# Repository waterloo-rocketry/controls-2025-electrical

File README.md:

2025 Controls Electrical Design
===============================

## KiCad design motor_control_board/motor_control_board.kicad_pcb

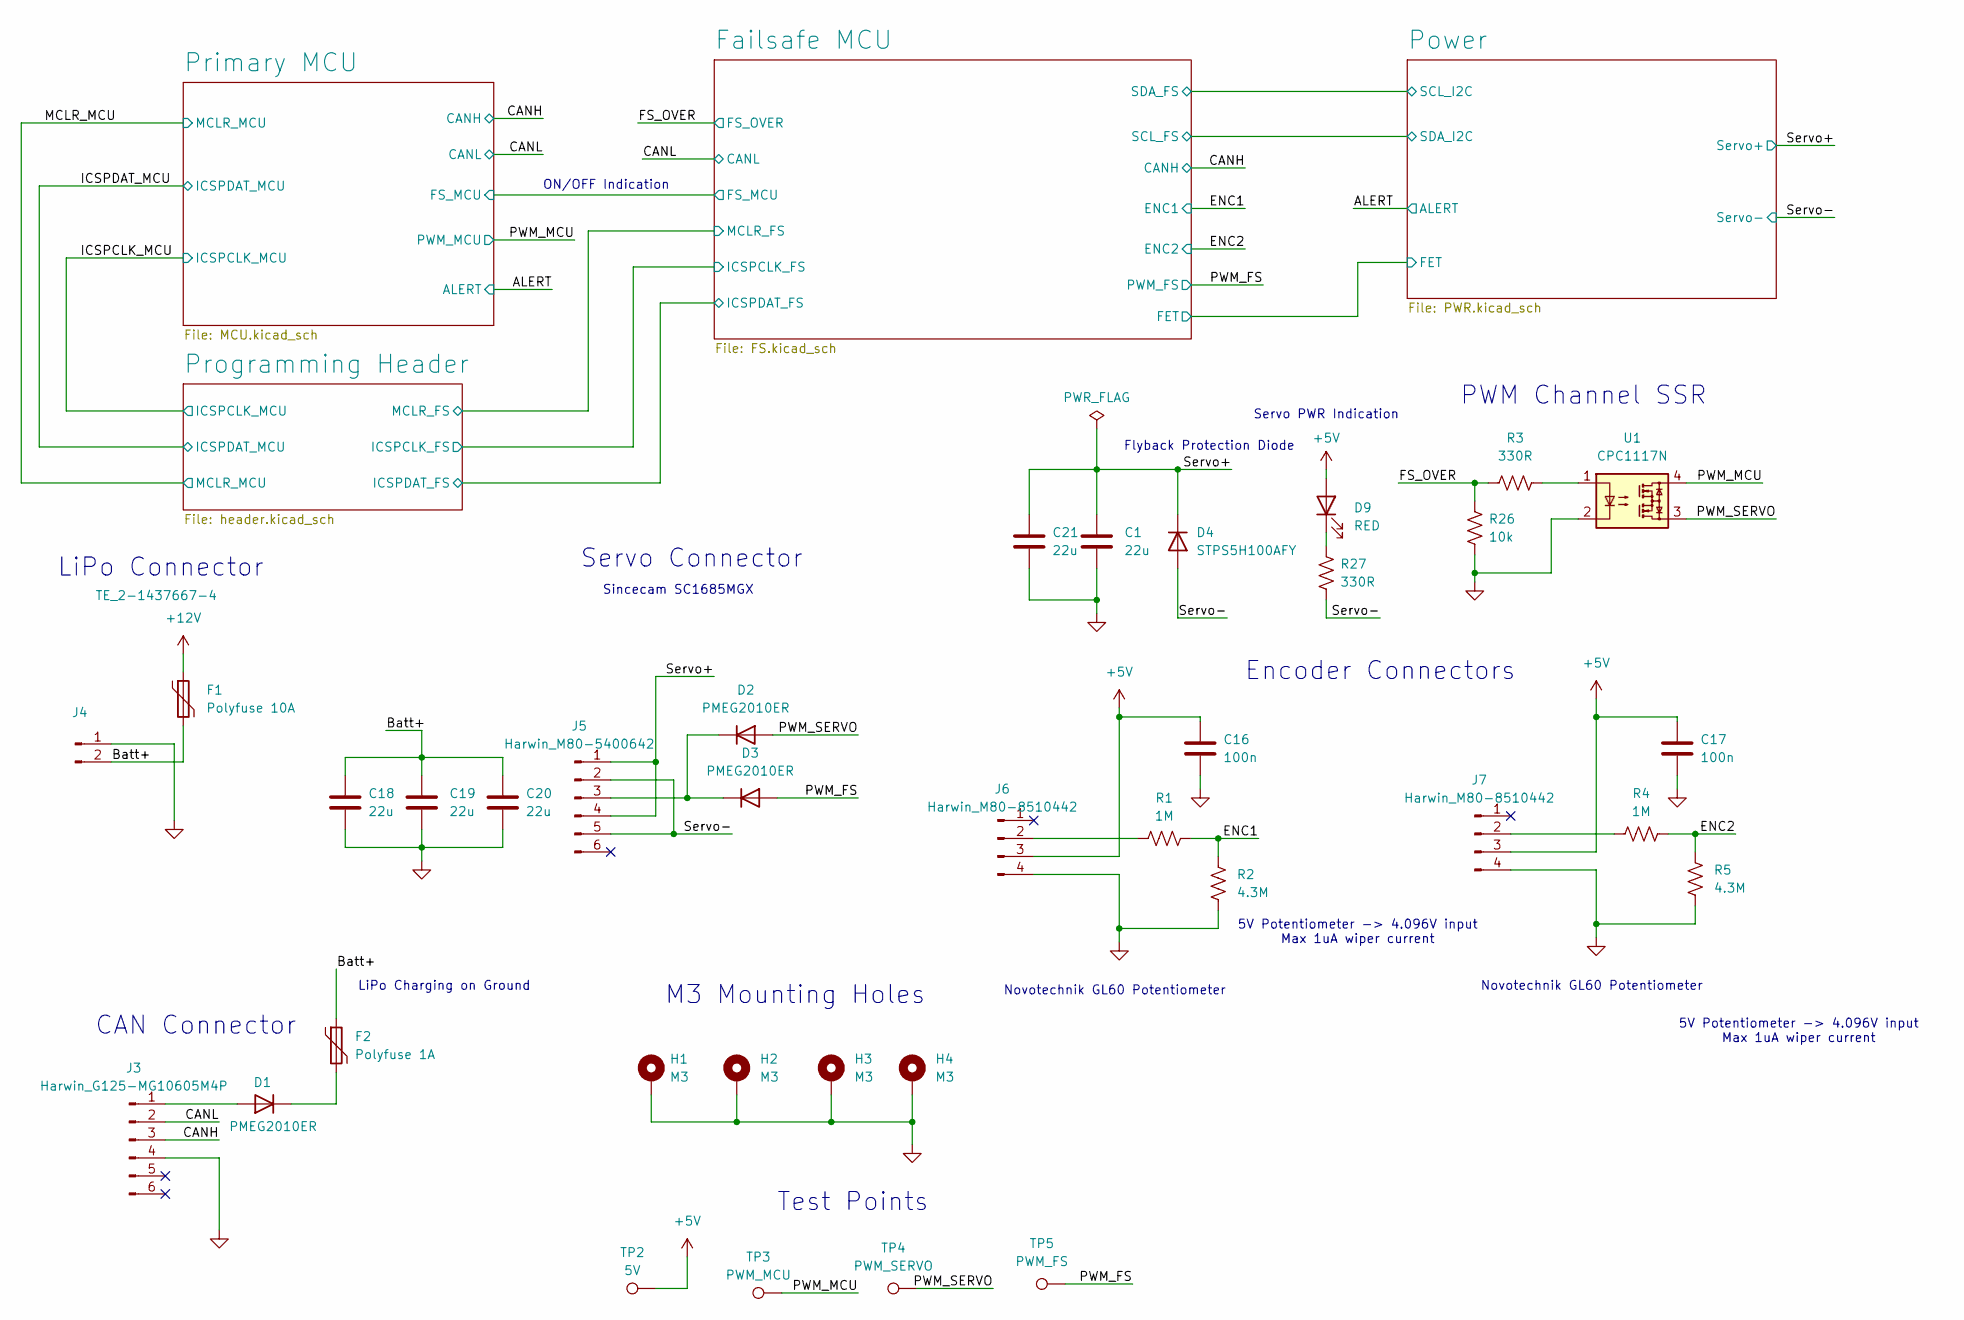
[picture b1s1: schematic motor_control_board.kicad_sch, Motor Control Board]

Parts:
C1, C18, C19, C20, C21: 22u; C_0805_2012Metric_Pad1.18x1.45mm_HandSolder
C16, C17: 100n; C_0805_2012Metric_Pad1.18x1.45mm_HandSolder
D1, D2, D3: PMEG2010ER; Nexperia_CFP3_SOD-123W
D4: STPS5H100AFY; D_SOD-128
D9: RED; LED_1206_3216Metric_Pad1.42x1.75mm_HandSolder
F1: Polyfuse 10A; Fuse_1206_3216Metric_Pad1.42x1.75mm_HandSolder
F2: Polyfuse 1A; Fuse_1206_3216Metric_Pad1.42x1.75mm_HandSolder
H1, H2, H3, H4: M3; MountingHole_3.2mm_M3_DIN965_Pad
J3: Harwin_G125-MG10605M4P; connector_Harwin_G125–MG10605M4P
J4: TE_2-1437667-4
J5: Harwin_M80-5400642; HARWIN_M80-5400642
J6, J7: Harwin_M80-8510442; HARWIN_M80-8510442
R1, R4: 1M; R_0805_2012Metric_Pad1.20x1.40mm_HandSolder
R2, R5: 4.3M; R_0805_2012Metric_Pad1.20x1.40mm_HandSolder
R3, R27: 330R; R_0805_2012Metric_Pad1.20x1.40mm_HandSolder
R26: 10k; R_0805_2012Metric_Pad1.20x1.40mm_HandSolder
TP2: 5V; TestPoint_Keystone_5000-5004_Miniature
TP3: PWM_MCU; TestPoint_Keystone_5000-5004_Miniature
TP4: PWM_SERVO; TestPoint_Keystone_5000-5004_Miniature
TP5: PWM_FS; TestPoint_Keystone_5000-5004_Miniature
U1: CPC1117N; SOIC254P610X218-4N

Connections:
+5V: C16.1, C17.1, D9.2 (A), J6.3, J7.3, TP2.1; also elsewhere on the board
+12V: F1.1; also elsewhere on the board
/Batt+: C18.1, C19.1, C20.1, F1.2, F2.1, J4.2
/CANH: J3.3; also elsewhere on the board
/CANL: J3.2; also elsewhere on the board
/ENC1: R1.2, R2.1; also elsewhere on the board
/ENC2: R4.2, R5.1; also elsewhere on the board
/FS_OVER: R3.1, R26.1; also elsewhere on the board
/PWM_FS: D3.2 (A), TP5.1; also elsewhere on the board
/PWM_MCU: TP3.1, U1.4; also elsewhere on the board
/PWM_SERVO: D2.2 (A), TP4.1, U1.3
/Servo+: C1.1, C21.1, D4.1 (K), J5.1, J5.4; also elsewhere on the board
/Servo-: D4.2 (A), J5.2, J5.5, R27.2; also elsewhere on the board
GND: C1.2, C16.2, C17.2, C18.2, C19.2, C20.2, C21.2, H1.1, H2.1, H3.1, H4.1, J3.4, J4.1, J6.4, J7.4, R2.2, R5.2, R26.2, U1.2; also elsewhere on the board
unnamed: D1.2 (A), J3.1
unnamed: D1.1 (K), F2.2
unnamed: D2.1 (K), D3.1 (K), J5.3
unnamed: D9.1 (K), R27.1
unnamed: J6.2, R1.1
unnamed: J7.2, R4.1
unnamed: R3.2, U1.1

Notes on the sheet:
Novotechnik GL60 Potentiometer
5V Potentiometer -> 4.096V input Max 1uA wiper current
Flyback Protection Diode
Servo PWR Indication
Servo Connector
M3 Mounting Holes
LiPo Charging on Ground
Sincecam SC1685MGX
ON/OFF Indication
Test Points
PWM Channel SSR
LiPo Connector
Encoder Connectors
CAN Connector

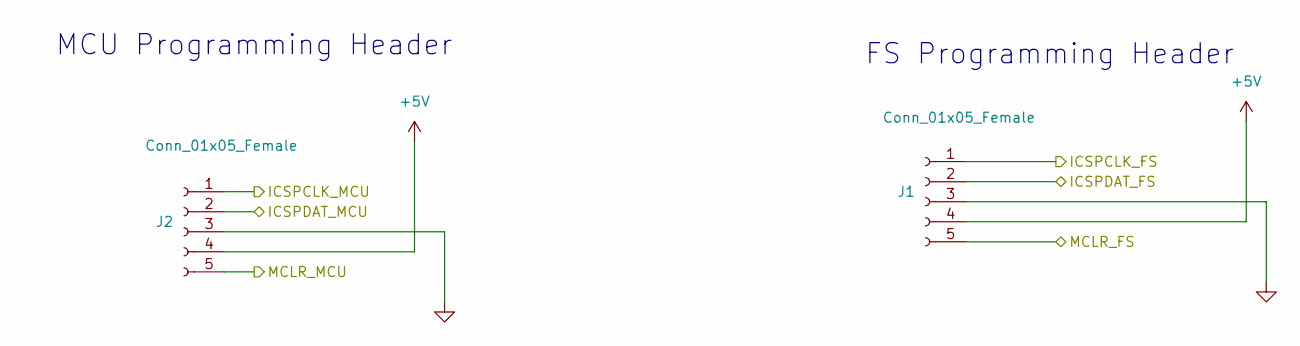
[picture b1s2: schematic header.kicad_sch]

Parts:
J1, J2: Conn_01x05_Female; PinSocket_5x2.54_SMD_90deg_952-3198-1-ND

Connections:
+5V: J1.4, J2.4; also elsewhere on the board
/Failsafe MCU/ICSPCLK_FS: J1.1; also elsewhere on the board
/Failsafe MCU/ICSPDAT_FS: J1.2; also elsewhere on the board
/Failsafe MCU/MCLR_FS: J1.5; also elsewhere on the board
/ICSPCLK_MCU: J2.1; also elsewhere on the board
/ICSPDAT_MCU: J2.2; also elsewhere on the board
/MCLR_MCU: J2.5; also elsewhere on the board
GND: J1.3, J2.3; also elsewhere on the board

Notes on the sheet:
FS Programming Header
MCU Programming Header

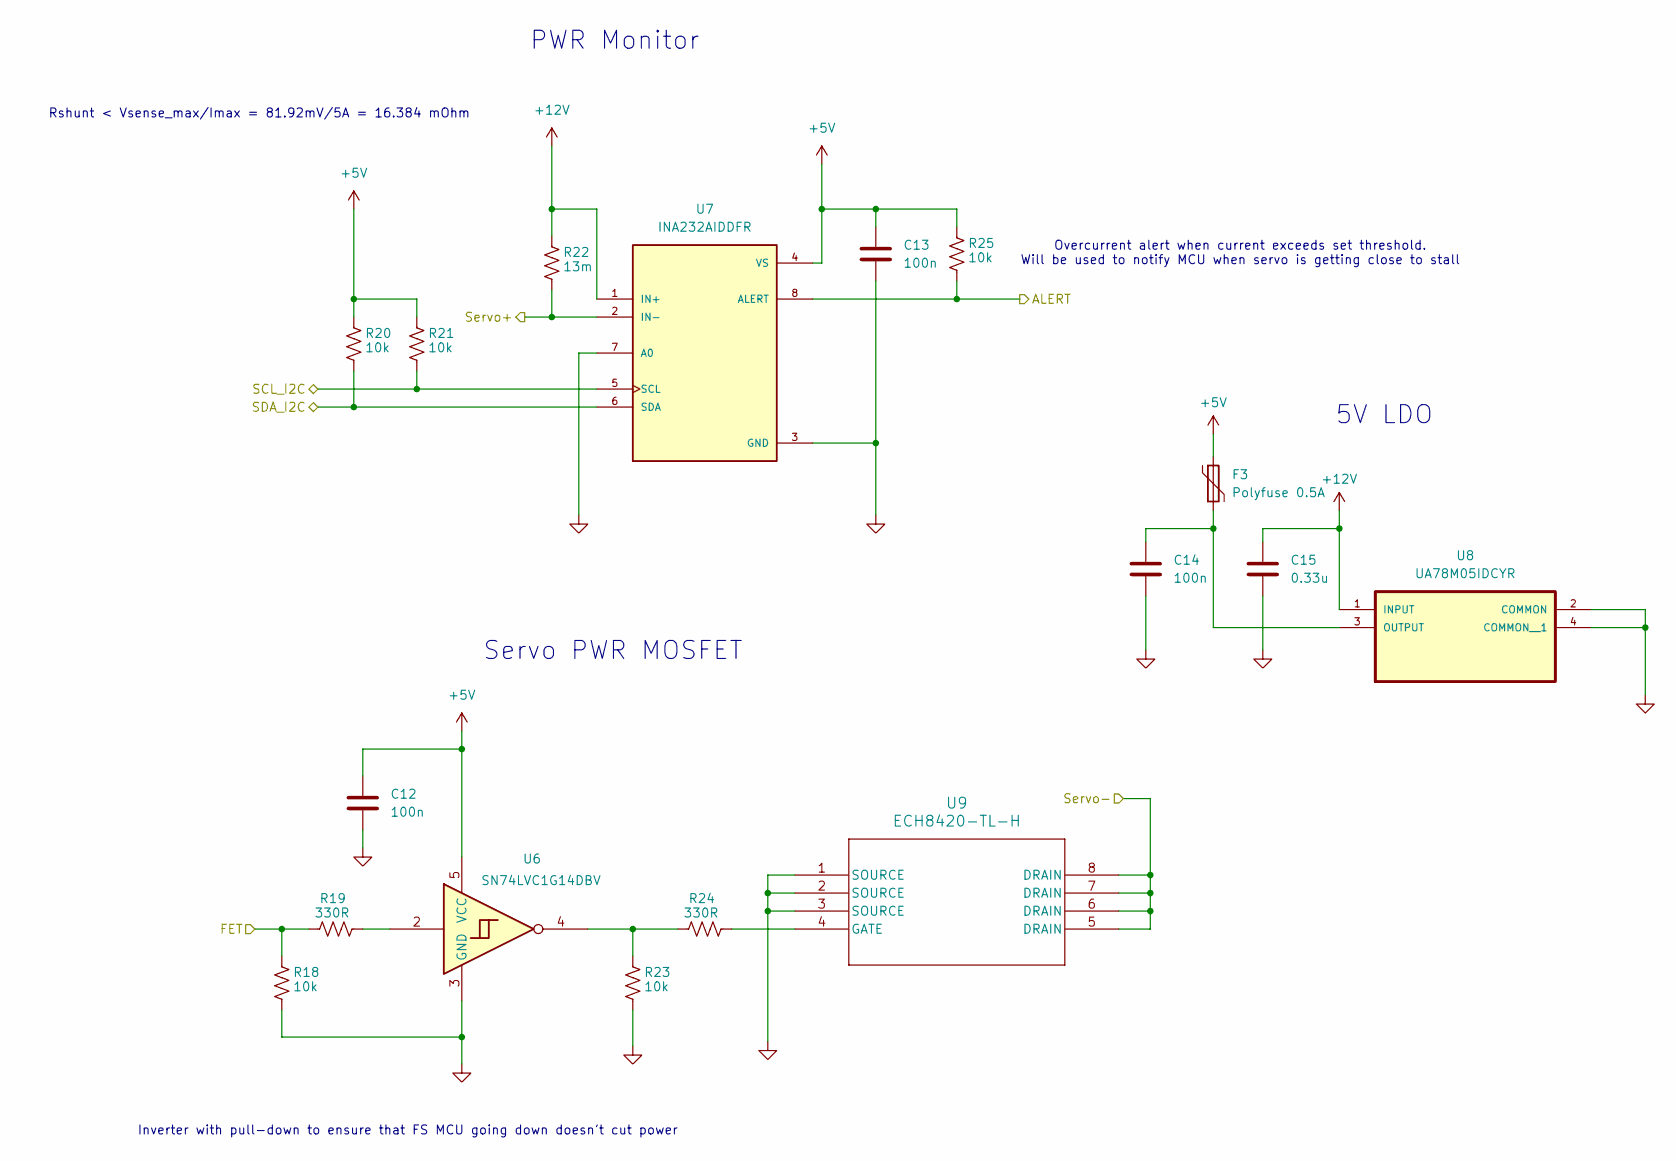
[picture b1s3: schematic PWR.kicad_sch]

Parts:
C12, C13, C14: 100n; C_0805_2012Metric_Pad1.18x1.45mm_HandSolder
C15: 0.33u; C_0805_2012Metric_Pad1.18x1.45mm_HandSolder
F3: Polyfuse 0.5A; Fuse_1206_3216Metric_Pad1.42x1.75mm_HandSolder
R18, R20, R21, R23, R25: 10k; R_0805_2012Metric_Pad1.20x1.40mm_HandSolder
R19, R24: 330R; R_0805_2012Metric_Pad1.20x1.40mm_HandSolder
R22: 13m; R_1206_3216Metric_Pad1.30x1.75mm_HandSolder
U6: SN74LVC1G14DBV; SOT-23-5
U7: INA232AIDDFR; SOT65P280X110-8N; PARTREV December 2022
U8: UA78M05IDCYR; SOT230P700X180-4N
U9: ECH8420-TL-H; OnSemi_ECH8

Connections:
+5V: C12.1, C13.1, F3.1, R20.1, R21.1, R25.1, U6.5 (VCC), U7.4 (VS); also elsewhere on the board
+12V: C15.1, R22.1, U7.1 (IN+), U8.1 (INPUT); also elsewhere on the board
/ALERT: R25.2, U7.8 (ALERT); also elsewhere on the board
/Failsafe MCU/FET: R18.1, R19.1; also elsewhere on the board
/Failsafe MCU/SCL_FS: R20.2, U7.6 (SDA); also elsewhere on the board
/Failsafe MCU/SDA_FS: R21.2, U7.5 (SCL); also elsewhere on the board
/Servo+: R22.2, U7.2 (IN-); also elsewhere on the board
/Servo-: U9.5 (DRAIN), U9.6 (DRAIN), U9.7 (DRAIN), U9.8 (DRAIN); also elsewhere on the board
GND: C12.2, C13.2, C14.2, C15.2, R18.2, R23.2, U6.3 (GND), U7.3 (GND), U7.7 (A0), U8.2 (COMMON), U8.4 (COMMON__1), U9.1 (SOURCE), U9.2 (SOURCE), U9.3 (SOURCE); also elsewhere on the board
unnamed: R19.2, U6.2
unnamed: R23.1, R24.1, U6.4
unnamed: C14.1, F3.2, U8.3 (OUTPUT)
unnamed: R24.2, U9.4 (GATE)

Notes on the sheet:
Servo PWR MOSFET
PWR Monitor
Inverter with pull-down to ensure that FS MCU going down doesn't cut power
5V LDO
Overcurrent alert when current exceeds set threshold. Will be used to notify MCU when servo is getting close to stall
Rshunt < Vsense_max/Imax = 81.92mV/5A = 16.384 mOhm

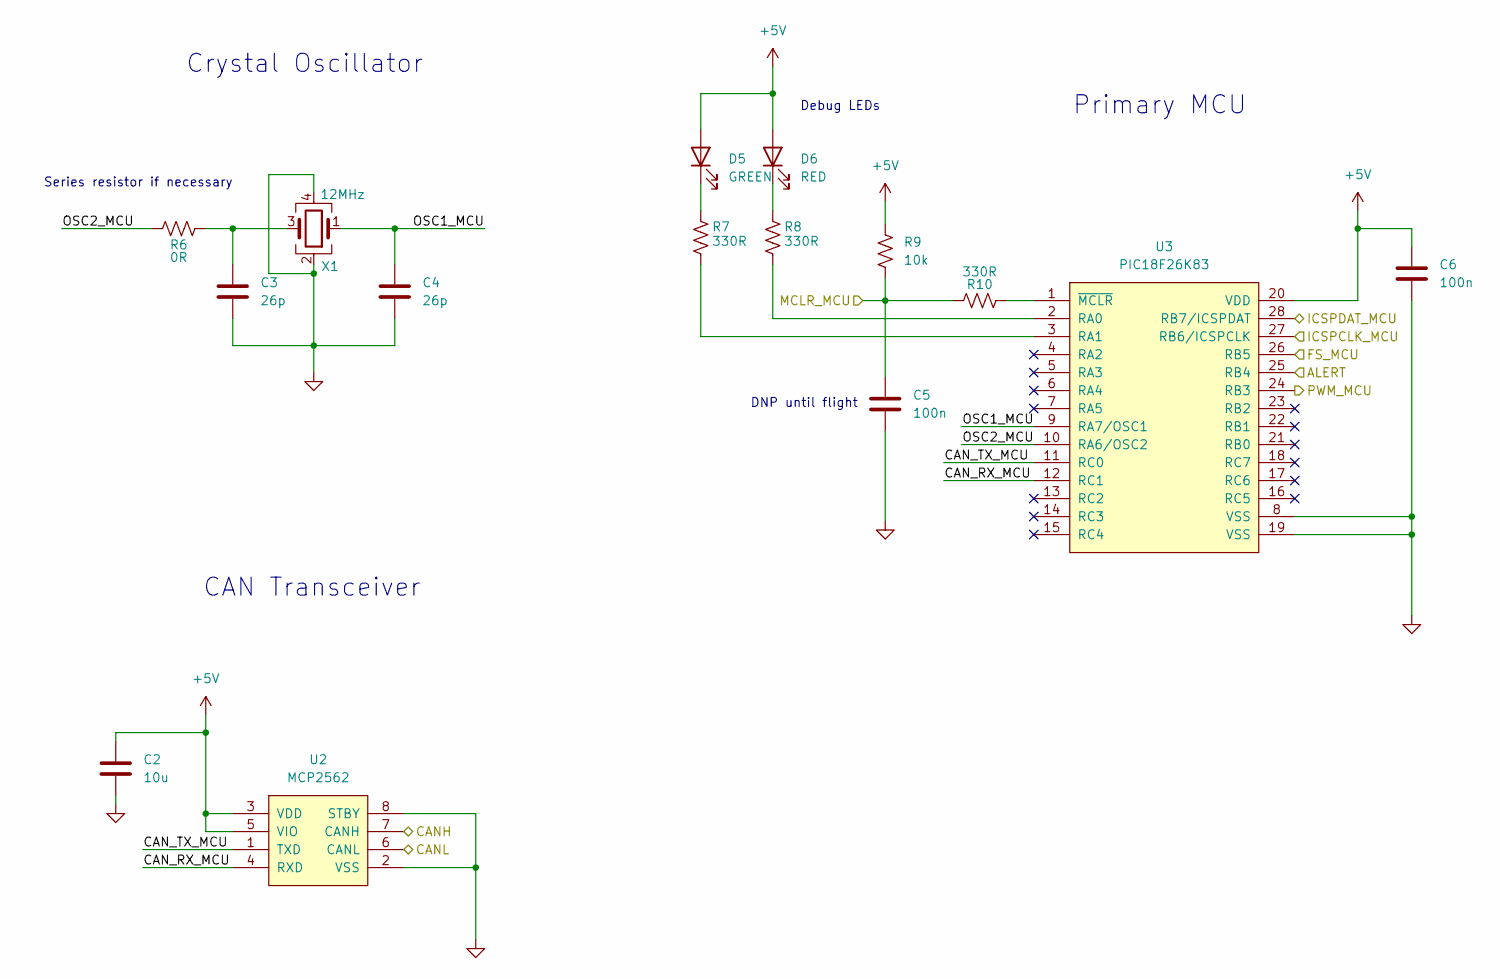
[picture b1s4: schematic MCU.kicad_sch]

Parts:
C2: 10u; C_0805_2012Metric_Pad1.18x1.45mm_HandSolder
C3, C4: 26p; C_0805_2012Metric_Pad1.18x1.45mm_HandSolder
C5, C6: 100n; C_0805_2012Metric_Pad1.18x1.45mm_HandSolder
D5: GREEN; LED_1206_3216Metric_Pad1.42x1.75mm_HandSolder
D6: RED; LED_1206_3216Metric_Pad1.42x1.75mm_HandSolder
R6: 0R; R_0805_2012Metric_Pad1.20x1.40mm_HandSolder
R7, R8, R10: 330R; R_0805_2012Metric_Pad1.20x1.40mm_HandSolder
R9: 10k; R_0805_2012Metric_Pad1.20x1.40mm_HandSolder
U2: MCP2562; SOIC-8_3.9x4.9mm_P1.27mm
U3: PIC18F26K83; SSOP-28_5.3x10.2mm_P0.65mm
X1: 12MHz; Crystal_SMD_Abracon_ABM8G-4Pin_3.2x2.5mm

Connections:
+5V: C2.1, C6.1, D5.2 (A), D6.2 (A), R9.1, U2.3 (VDD), U2.5 (VIO), U3.20 (VDD); also elsewhere on the board
/ALERT: U3.25 (RB4); also elsewhere on the board
/CANH: U2.7 (CANH); also elsewhere on the board
/CANL: U2.6 (CANL); also elsewhere on the board
/Failsafe MCU/FS_MCU: U3.26 (RB5); also elsewhere on the board
/ICSPCLK_MCU: U3.27 (RB6/ICSPCLK); also elsewhere on the board
/ICSPDAT_MCU: U3.28 (RB7/ICSPDAT); also elsewhere on the board
/MCLR_MCU: C5.1, R9.2, R10.2; also elsewhere on the board
/PWM_MCU: U3.24 (RB3); also elsewhere on the board
/Primary MCU/CAN_RX_MCU: U2.4 (RXD), U3.12 (RC1)
/Primary MCU/CAN_TX_MCU: U2.1 (TXD), U3.11 (RC0)
/Primary MCU/OSC1_MCU: C4.1, U3.9 (RA7/OSC1), X1.1
/Primary MCU/OSC2_MCU: R6.1, U3.10 (RA6/OSC2)
GND: C2.2, C3.2, C4.2, C5.2, C6.2, U2.2 (VSS), U2.8 (STBY), U3.8 (VSS), U3.19 (VSS), X1.2, X1.4; also elsewhere on the board
unnamed: C3.1, R6.2, X1.3
unnamed: D5.1 (K), R7.1
unnamed: D6.1 (K), R8.1
unnamed: R8.2, U3.2 (RA0)
unnamed: R7.2, U3.3 (RA1)
unnamed: R10.1, U3.1 (~MCLR)

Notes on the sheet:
DNP until flight
Series resistor if necessary
Crystal Oscillator
Primary MCU
CAN Transceiver
Debug LEDs

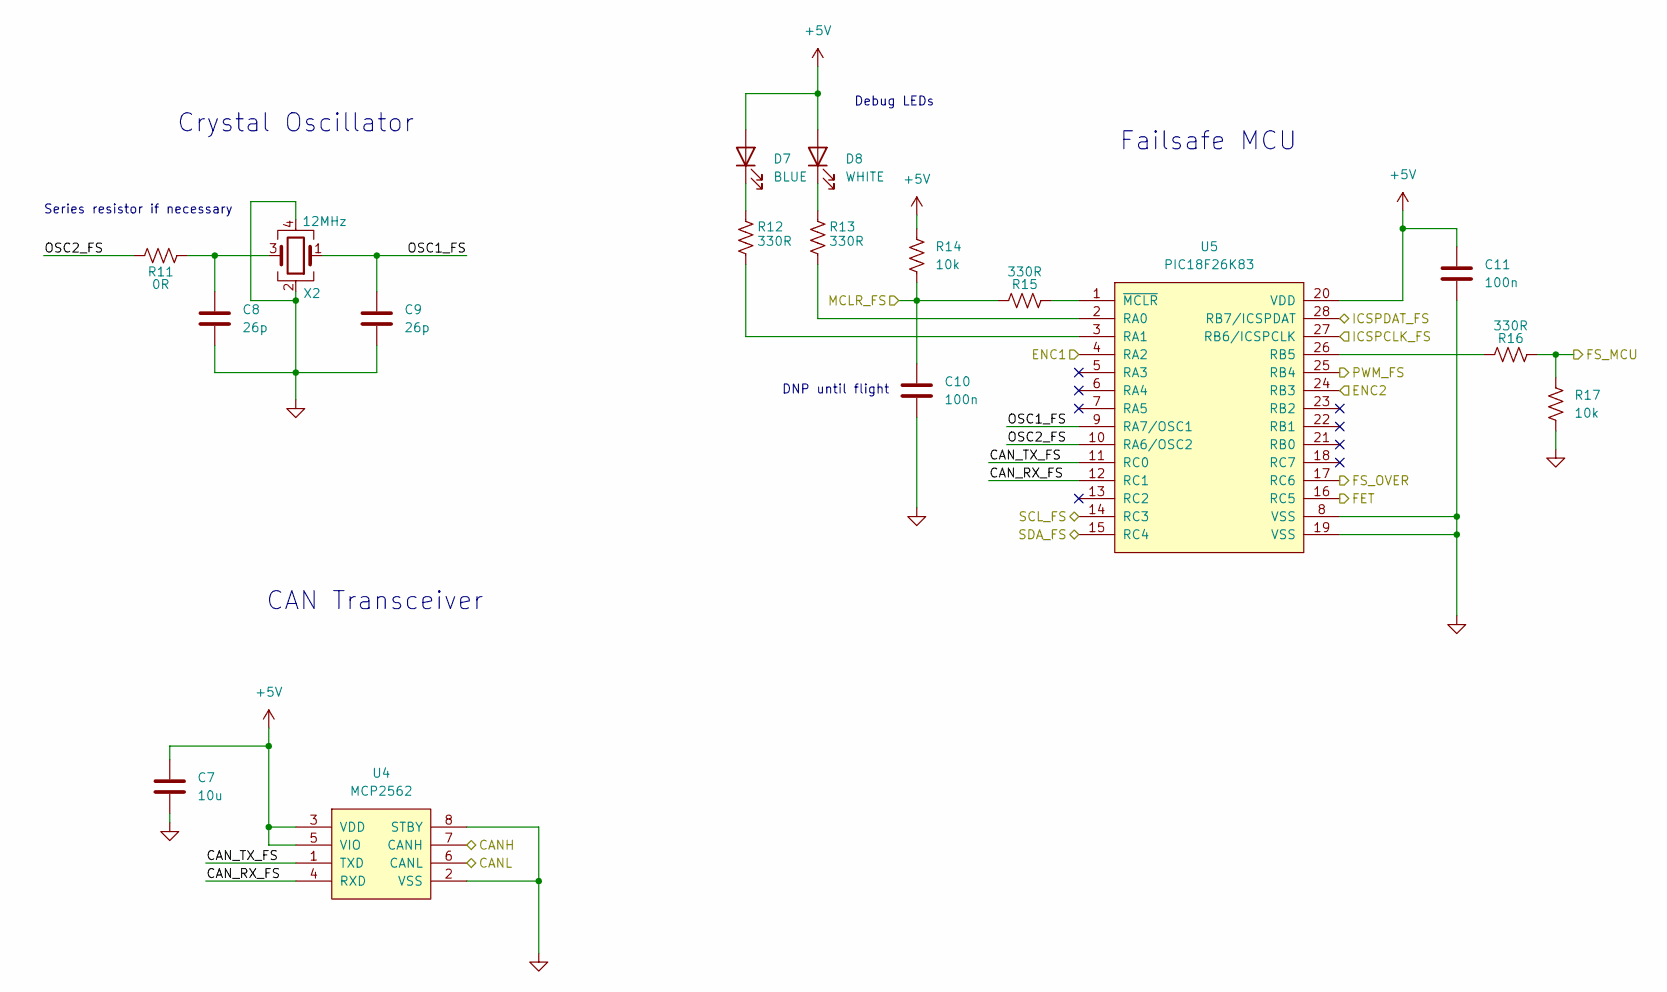
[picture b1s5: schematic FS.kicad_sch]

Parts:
C7: 10u; C_0805_2012Metric_Pad1.18x1.45mm_HandSolder
C8, C9: 26p; C_0805_2012Metric_Pad1.18x1.45mm_HandSolder
C10, C11: 100n; C_0805_2012Metric_Pad1.18x1.45mm_HandSolder
D7: BLUE; LED_1206_3216Metric_Pad1.42x1.75mm_HandSolder
D8: WHITE; LED_1206_3216Metric_Pad1.42x1.75mm_HandSolder
R11: 0R; R_0805_2012Metric_Pad1.20x1.40mm_HandSolder
R12, R13, R15, R16: 330R; R_0805_2012Metric_Pad1.20x1.40mm_HandSolder
R14, R17: 10k; R_0805_2012Metric_Pad1.20x1.40mm_HandSolder
U4: MCP2562; SOIC-8_3.9x4.9mm_P1.27mm
U5: PIC18F26K83; SSOP-28_5.3x10.2mm_P0.65mm
X2: 12MHz; Crystal_SMD_Abracon_ABM8G-4Pin_3.2x2.5mm

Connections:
+5V: C7.1, C11.1, D7.2 (A), D8.2 (A), R14.1, U4.3 (VDD), U4.5 (VIO), U5.20 (VDD); also elsewhere on the board
/CANH: U4.7 (CANH); also elsewhere on the board
/CANL: U4.6 (CANL); also elsewhere on the board
/ENC1: U5.4 (RA2); also elsewhere on the board
/ENC2: U5.24 (RB3); also elsewhere on the board
/FS_OVER: U5.17 (RC6); also elsewhere on the board
/Failsafe MCU/CAN_RX_FS: U4.4 (RXD), U5.12 (RC1)
/Failsafe MCU/CAN_TX_FS: U4.1 (TXD), U5.11 (RC0)
/Failsafe MCU/FET: U5.16 (RC5); also elsewhere on the board
/Failsafe MCU/FS_MCU: R16.1, R17.1; also elsewhere on the board
/Failsafe MCU/ICSPCLK_FS: U5.27 (RB6/ICSPCLK); also elsewhere on the board
/Failsafe MCU/ICSPDAT_FS: U5.28 (RB7/ICSPDAT); also elsewhere on the board
/Failsafe MCU/MCLR_FS: C10.1, R14.2, R15.2; also elsewhere on the board
/Failsafe MCU/OSC1_FS: C9.1, U5.9 (RA7/OSC1), X2.1
/Failsafe MCU/OSC2_FS: R11.1, U5.10 (RA6/OSC2)
/Failsafe MCU/SCL_FS: U5.14 (RC3); also elsewhere on the board
/Failsafe MCU/SDA_FS: U5.15 (RC4); also elsewhere on the board
/PWM_FS: U5.25 (RB4); also elsewhere on the board
GND: C7.2, C8.2, C9.2, C10.2, C11.2, R17.2, U4.2 (VSS), U4.8 (STBY), U5.8 (VSS), U5.19 (VSS), X2.2, X2.4; also elsewhere on the board
unnamed: C8.1, R11.2, X2.3
unnamed: D7.1 (K), R12.1
unnamed: D8.1 (K), R13.1
unnamed: R13.2, U5.2 (RA0)
unnamed: R12.2, U5.3 (RA1)
unnamed: R16.2, U5.26 (RB5)
unnamed: R15.1, U5.1 (~MCLR)

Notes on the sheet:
Failsafe MCU
Crystal Oscillator
CAN Transceiver
Debug LEDs
DNP until flight
Series resistor if necessary

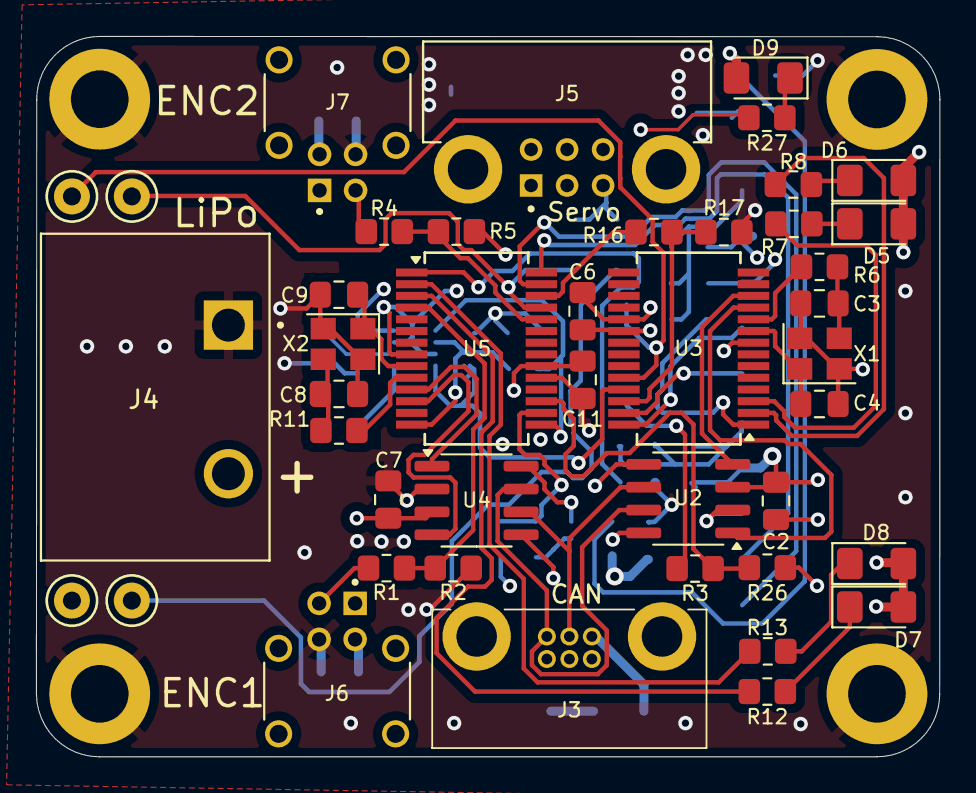
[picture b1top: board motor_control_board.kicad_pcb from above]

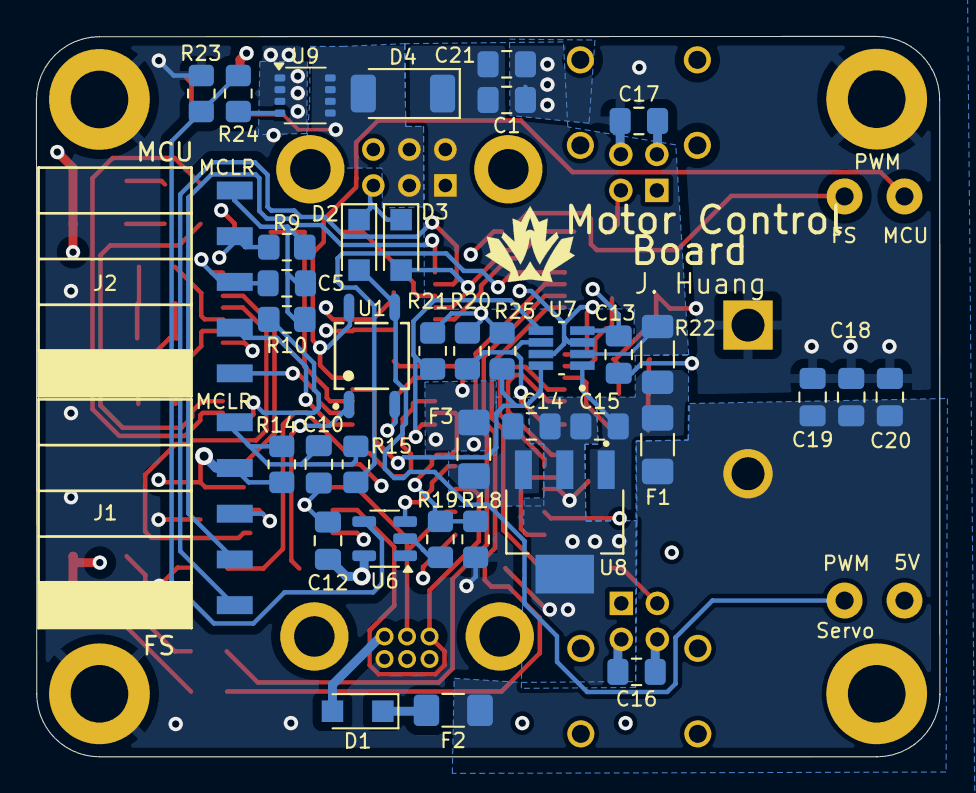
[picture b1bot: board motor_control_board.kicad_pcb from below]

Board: 4 copper layers, 50.2 x 40.0 mm, 86 parts (39 on the bottom side), 57 nets.

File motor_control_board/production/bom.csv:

Designator,Footprint,Quantity,Value,LCSC Part #
"C1, C18, C19, C20, C21",0805,5,22u,
"C10, C11, C12, C13, C14, C16, C17, C5, C6",0805,9,100n,
C15,0805,1,0.33u,
"C2, C7",0805,2,10u,
"C3, C4, C8, C9",0805,4,26p,
"D1, D2, D3",Nexperia_CFP3_SOD-123W,3,PMEG2010ER,
D4,D_SOD-128,1,STPS5H100AFY,
D5,1206,1,GREEN,
"D6, D9",1206,2,RED,
D7,1206,1,BLUE,
D8,1206,1,WHITE,
F1,1206,1,Polyfuse 10A,
F2,1206,1,Polyfuse 1A,
F3,1206,1,Polyfuse 0.5A,
"J1, J2",PinSocket_5x2.54_SMD_90deg_952-3198-1-ND,2,Conn_01x05_Female,
J3,connector_Harwin_G125–MG10605M4P,1,Harwin_G125-MG10605M4P,
J4,TE_2-1437667-4,1,Harwin_M80-5000000M5-02-333-00-000,
J5,HARWIN_M80-5400642,1,Harwin_M80-5400642,
"J6, J7",HARWIN_M80-8510442,2,Harwin_M80-8510442,
"R1, R4",0805,2,1M,
"R10, R12, R13, R15, R16, R19, R24, R27, R3, R7, R8",0805,11,330R,
"R11, R6",0805,2,0R,
"R14, R17, R18, R20, R21, R23, R25, R26, R9",0805,9,10k,
"R2, R5",0805,2,4.3M,
R22,1206,1,13m,
TP2,TestPoint_Keystone_5000-5004_Miniature,1,5V,
TP3,TestPoint_Keystone_5000-5004_Miniature,1,PWM_MCU,
TP4,TestPoint_Keystone_5000-5004_Miniature,1,PWM_SERVO,
TP5,TestPoint_Keystone_5000-5004_Miniature,1,PWM_FS,
U1,SOIC254P610X218-4N,1,CPC1117N,
"U2, U4",SOIC-8_3.9x4.9mm_P1.27mm,2,MCP2562,
"U3, U5",SSOP-28_5.3x10.2mm_P0.65mm,2,PIC18F26K83,
U6,SOT-23-5,1,SN74LVC1G14DBV,
U7,SOT65P280X110-8N,1,INA232AIDDFR,
U8,SOT230P700X180-4N,1,UA78M05IDCYR,
U9,OnSemi_ECH8,1,ECH8420-TL-H,
"X1, X2",Crystal_SMD_Abracon_ABM8G-4Pin_3.2x2.5mm,2,12MHz,

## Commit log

2024-11-11 Updated footprints
2024-11-11 completed schematic
2024-11-18 Minor schematic edits
    Annotated schematic, selected mosfet and diodes, addressed comments
2024-11-23 Added second encoder connection, minor edits
2024-11-23 assigned footprints
2024-11-24 components placed
2024-11-24 PCB routing 70% done
2024-11-26 Routing Complete
2024-11-26 Silkscreen and minor copper pour edits
2024-11-26 Fixed symbol and footprint libraries
2024-11-26 minor touchups
2024-11-26 Re-add kicad-footprints submodule on motor_control_board branch
2024-11-26 Fixed DRC errors except for the PTH keep out zones
2024-11-28 fixed footprints (hopefully)
2024-11-28 Fix Hole Keepout Errors
2024-11-28 I should save project before I open it
2024-11-28 Address DRC Warnings
2024-11-28 How does it know I have the file opened??
2024-11-29 Added servo power LED, bulk decoupling caps
2024-11-29 silkscreen
2024-11-29 Free some Real estate so Joe can move in
    Moved things around, generate production files
2024-11-30 Fix DRC warnings
2024-11-30 skill issued two pinouts
2024-11-30 Address concerns
2024-12-02 addressed concerns
2024-12-02 production files
2024-12-02 minor schematic and copper pour cleanup
2024-12-02 updated production files
2024-12-02 moved via for finn
2024-12-03 Motor Control Board
